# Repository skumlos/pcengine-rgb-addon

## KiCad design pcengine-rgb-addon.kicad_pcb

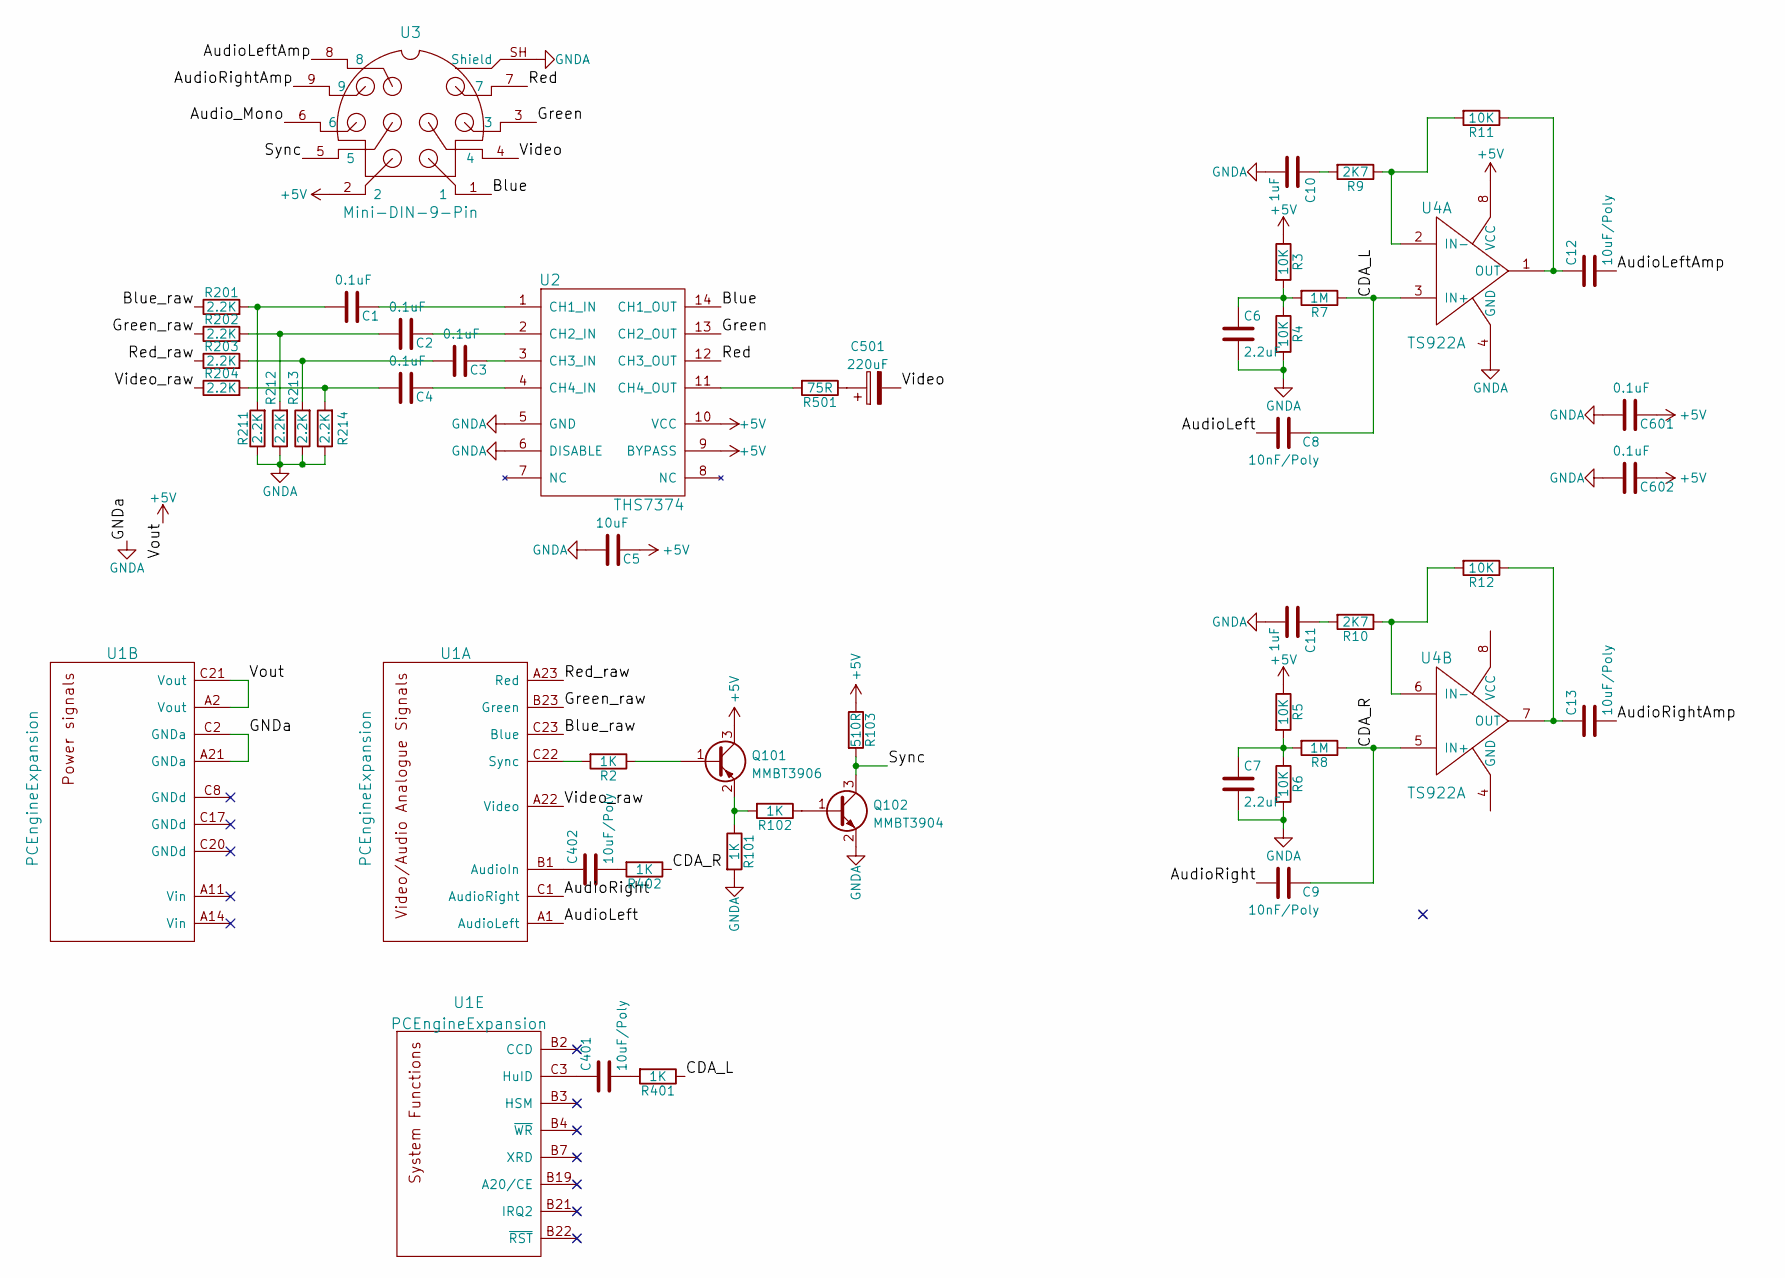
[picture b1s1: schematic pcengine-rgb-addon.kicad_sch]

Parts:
C1, C2, C3, C4, C601, C602: 0.1uF; C_0603_1608Metric_Pad1.08x0.95mm_HandSolder
C5: 10uF; C_0805_2012Metric_Pad1.18x1.45mm_HandSolder
C6, C7: 2.2uF; C_0603_1608Metric_Pad1.08x0.95mm_HandSolder
C8, C9: 10nF/Poly; C_Rect_L7.2mm_W2.5mm_P5.00mm_FKS2_FKP2_MKS2_MKP2
C10, C11: 1uF; C_0603_1608Metric_Pad1.08x0.95mm_HandSolder
C12: 10uF/Poly; CP_Elec_4x5.3
C13, C401, C402: 10uF/Poly; CP_Elec_4x5.3; Partnumber UWX1V100MCL1GB
C501: 220uF; CP_EIA-3528-12_Kemet-T_Pad1.50x2.35mm_HandSolder
Q101: MMBT3906; SOT-23
Q102: MMBT3904; SOT-23
R2, R101, R102, R401, R402: 1K; R_0603_1608Metric_Pad0.98x0.95mm_HandSolder
R3, R4, R5, R6, R11, R12: 10K; R_0603_1608Metric_Pad0.98x0.95mm_HandSolder
R7, R8: 1M; R_0603_1608Metric_Pad0.98x0.95mm_HandSolder
R9, R10: 2K7; R_0603_1608Metric_Pad0.98x0.95mm_HandSolder
R103: 510R; R_0603_1608Metric_Pad0.98x0.95mm_HandSolder
R201, R202, R203, R204, R211, R212, R213, R214: 2.2K; R_0603_1608Metric_Pad0.98x0.95mm_HandSolder
R501: 75R; R_0603_1608Metric_Pad0.98x0.95mm_HandSolder
U1: PCEngineExpansion; Partnumber SSQ-123-02-T-T-RA
U2: THS7374; TSSOP-14_4.4x5mm_P0.65mm; Partnumber THS7374IPWR
U3: Mini-DIN-9-Pin; MINI-DIN-9PIN; Part number MDC-209
U4: TS922A; SOIC-8_3.9x4.9mm_Pitch1.27mm

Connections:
+5V: C5.1, C601.1, C602.1, Q101.3 (C), R3.1, R5.1, R103.1, U1.A2 (Vout), U1.C21 (Vout), U2.9 (BYPASS), U2.10 (VCC), U3.2, U4.8 (VCC)
/AudioLeft: C8.2, U1.A1 (AudioLeft)
/AudioLeftAmp: C12.2, U3.8
/AudioRight: C9.2, U1.C1 (AudioRight)
/AudioRightAmp: C13.2, U3.9
/Audio_Mono: U3.6
/Blue: U2.14 (CH1_OUT), U3.1
/Blue_raw: R201.1, U1.C23 (Blue)
/CDA_L: C8.1, R7.1, R401.1, U4.3 (IN+)
/CDA_R: C9.1, R8.1, R402.1, U4.5 (IN+)
/Green: U2.13 (CH2_OUT), U3.3
/Green_raw: R202.1, U1.B23 (Green)
/Red: U2.12 (CH3_OUT), U3.7
/Red_raw: R203.1, U1.A23 (Red)
/Sync: Q102.3 (C), R103.2, U3.5
/Video: C501.2, U3.4
/Video_raw: R204.1, U1.A22 (Video)
GNDA: C5.2, C6.2, C7.2, C10.2, C11.2, C601.2, C602.2, Q102.2 (E), R4.2, R6.2, R101.2, R211.1, R212.1, R213.1, R214.1, U1.A21 (GNDa), U1.C2 (GNDa), U2.5 (GND), U2.6 (DISABLE), U3.SH (Shield), U4.4 (GND)
unnamed: C1.1, U2.1 (CH1_IN)
unnamed: C1.2, R201.2, R211.2
unnamed: C2.1, U2.2 (CH2_IN)
unnamed: C2.2, R202.2, R212.2
unnamed: C3.1, U2.3 (CH3_IN)
unnamed: C3.2, R203.2, R213.2
unnamed: C4.1, U2.4 (CH4_IN)
unnamed: C4.2, R204.2, R214.2
unnamed: C6.1, R3.2, R4.1, R7.2
unnamed: C7.1, R5.2, R6.1, R8.2
unnamed: C10.1, R9.2
unnamed: C11.1, R10.2
unnamed: C12.1, R11.1, U4.1 (OUT)
unnamed: C13.1, R12.1, U4.7 (OUT)
unnamed: C401.1, U1.C3 (HuID)
unnamed: C401.2, R401.2
unnamed: C402.1, U1.B1 (AudioIn)
unnamed: C402.2, R402.2
unnamed: Q101.1 (B), R2.1
unnamed: Q101.2 (E), R101.1, R102.2
unnamed: Q102.1 (B), R102.1
unnamed: R2.2, U1.C22 (Sync)
unnamed: R10.1, R12.2, U4.6 (IN-)
unnamed: R9.1, R11.2, U4.2 (IN-)
unnamed: C501.1, R501.1
unnamed: R501.2, U2.11 (CH4_OUT)

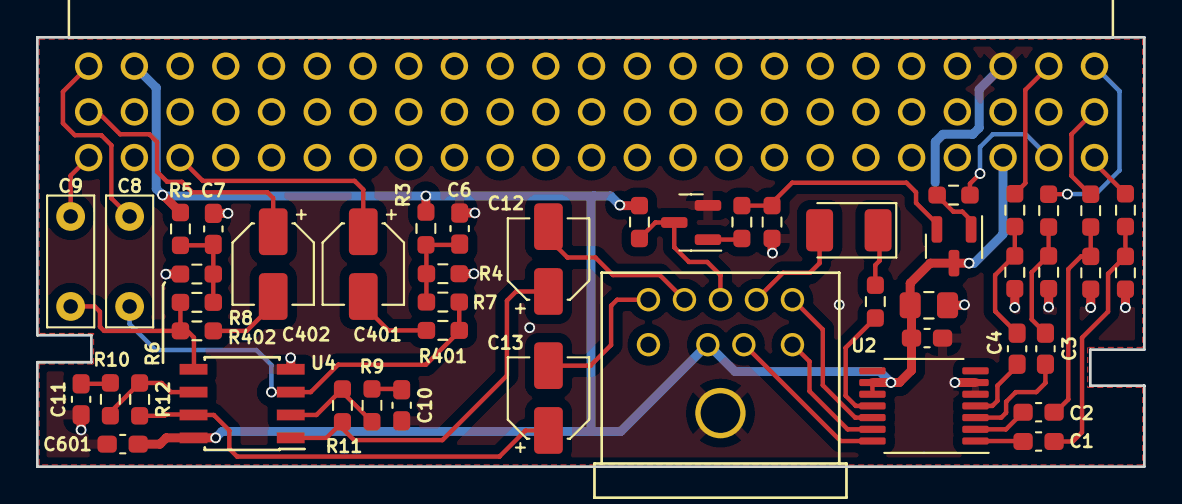
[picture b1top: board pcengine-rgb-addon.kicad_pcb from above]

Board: 2 copper layers, 61.5 x 23.8 mm, 49 parts (0 on the bottom side), 43 nets.

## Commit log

2023-06-04 Initial Rev. C
